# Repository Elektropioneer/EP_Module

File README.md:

# EP_Module

In this repo you can find our custom module for the main board.

## The raw module:

<!-- 

-->

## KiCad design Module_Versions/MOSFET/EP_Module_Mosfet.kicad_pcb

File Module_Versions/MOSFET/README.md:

# MOSFET module

This module contains 3xBS170 mosfets.

## Top View 3D

## Bottom View 3D

## PCB Raw

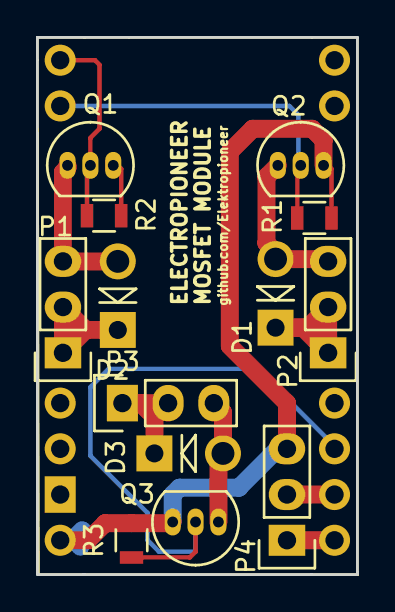
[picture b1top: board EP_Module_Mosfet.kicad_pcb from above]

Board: 2 copper layers, 17.8 x 29.8 mm, 14 parts (0 on the bottom side), 12 nets.

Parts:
D1, D2, D3: D; Diode_DO-41_SOD81_Vertical_AnodeUp
P1, P2, P3, P4: CONN_01X03; Pin_Header_Straight_1x03
Q1, Q2, Q3: BS170; TO-92_Inline_Narrow_Oval
R1, R2, R3: R; R_0805
U1: EP_MODULE; EP_Module

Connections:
GND: P4.3, Q1.3, Q2.3, Q3.3, R1.2, R2.2, R3.2, U1.2
unnamed: D1.1, P2.1, P2.2
unnamed: D1.2, P2.3, Q2.1
unnamed: D2.1, P1.1, P1.2
unnamed: D2.2, P1.3, Q1.1
unnamed: D3.1, P3.1, P3.2
unnamed: D3.2, P3.3, Q3.1
PA6: P4.2, U1.11
PA7: P4.1, U1.12
PG0: Q1.2, R2.1, U1.3
PG1: Q2.2, R1.1, U1.4
PG2: Q3.2, R3.1, U1.5

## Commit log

2017-10-22 Added main files and pics
2017-10-22 Added 3d
2017-10-22 Modif to readme
2017-10-22 Changed the readme
2017-10-22 Added mosfet board with 3 mosfets, not finished, needs checking
2017-10-22 pdf typo
2017-10-22 Added readme for mosfet
